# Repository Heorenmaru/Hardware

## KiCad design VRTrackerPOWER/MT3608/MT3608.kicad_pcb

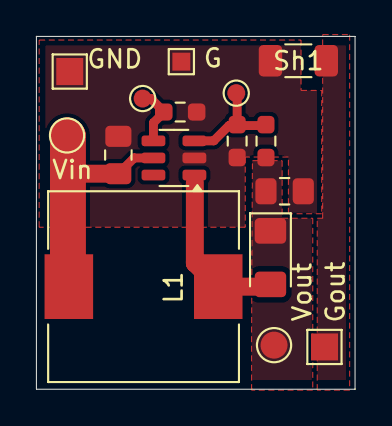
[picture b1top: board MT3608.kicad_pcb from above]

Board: 2 copper layers, 17.7 x 19.6 mm, 16 parts (0 on the bottom side), 7 nets.

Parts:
C2, C3: C; C_0805_2012Metric_Pad1.18x1.45mm_HandSolder
D2: D; D_1206_3216Metric_Pad1.42x1.75mm_HandSolder
E1: EN; TestPoint_Pad_D1.0mm
FB1: FB; TestPoint_Pad_D1.0mm
G: G; TestPoint_Pad_1.0x1.0mm
GND: GND; TestPoint_Pad_1.5x1.5mm
Gout: TestPoint_Pad_1.5x1.5mm
L1: L; L_10.4x10.4_H4.8
R2, R3, R4: R; R_0603_1608Metric_Pad0.98x0.95mm_HandSolder
Sh1: R; R_1206_3216Metric_Pad1.30x1.75mm_HandSolder
U1: MT3608; SOT-23-6
Vin: TestPoint_Pad_D1.5mm
Vout: TestPoint_Pad_D1.5mm

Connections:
unnamed: D2.2 (A), L1.2, U1.1 (SW)
unnamed: C3.1, D2.1 (K), R3.1, Vout.1
unnamed: Gout.1, Sh1.2
unnamed: E1.1, R2.1, U1.4 (EN)
unnamed: FB1.1, R3.2, R4.1, U1.3 (FB)
unnamed: C2.2, C3.2, G.1, GND.1, R2.2, R4.2, Sh1.1, U1.2 (GND)
unnamed: C2.1, L1.1, U1.5 (IN), Vin.1

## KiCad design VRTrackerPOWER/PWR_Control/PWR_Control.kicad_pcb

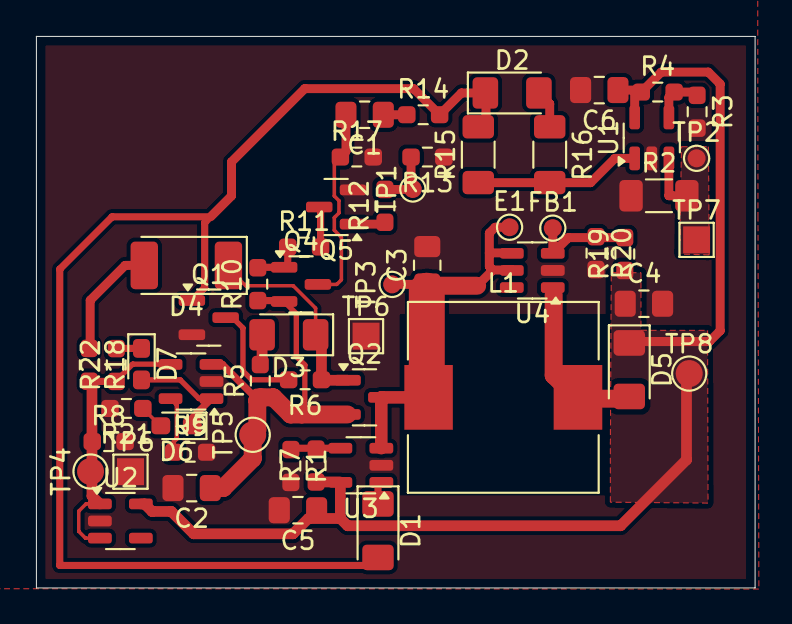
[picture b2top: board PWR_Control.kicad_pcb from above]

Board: 2 copper layers, 39.9 x 30.6 mm, 56 parts (0 on the bottom side), 28 nets.

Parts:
C1, C2, C3, C4, C5, C6: C; C_0805_2012Metric_Pad1.18x1.45mm_HandSolder
D1, D2, D3, D5: D; D_1206_3216Metric_Pad1.42x1.75mm_HandSolder
D4: D; D_2010_5025Metric_Pad1.52x2.65mm_HandSolder
D6, D7: LED; LED_0603_1608Metric_Pad1.05x0.95mm_HandSolder
E1: EN; TestPoint_Pad_D1.0mm
FB1: FB; TestPoint_Pad_D1.0mm
L1: L; L_10.4x10.4_H4.8
Q1, Q5: AO3400A; SOT-23
Q2, Q4: AO3401A; SOT-23
R1, R3, R4, R5, R6, R7, R8, R9, R10, R11, R12, R13, R14, R17, R18, R19, R20, R21, R22: R; R_0603_1608Metric_Pad0.98x0.95mm_HandSolder
R2: 0R5; R_1206_3216Metric_Pad1.30x1.75mm_HandSolder
R15, R16: R; R_1206_3216Metric_Pad1.30x1.75mm_HandSolder
TP1: CONTROL; TestPoint_Pad_D1.0mm
TP2: CUR; TestPoint_Pad_D1.0mm
TP3: PWR; TestPoint_Pad_D1.0mm
TP4: USB; TestPoint_Pad_D1.5mm
TP5: VBAT; TestPoint_Pad_D1.5mm
TP6, TP6#2: GNDi; TestPoint_Pad_1.5x1.5mm
TP7: GNDo; TestPoint_Pad_1.5x1.5mm
TP8: 5V_DC; TestPoint_Pad_D1.5mm
U1, U3: MCP6001-OT; SOT-23-5
U2: MAX40200AUK; SOT-23-5
U4: MT3608; SOT-23-6
U5: MCP73831-2-OT; SOT-23-5

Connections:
+3V6: C3.1, E1.1, L1.1, Q2.3 (D), TP3.1, U3.3 (+), U4.4 (EN), U4.5 (IN)
+3VB: C2.1, Q2.2 (S), Q4.2 (S), R5.1, R10.1, TP5.1, U5.3 (V_{BAT})
+5V: R8.1, R18.2, R22.1, TP4.1, U2.1 (VDD), U2.3 (EN), U5.4 (V_{DD})
+5VD: C4.1, C5.1, C6.1, D5.1 (K), R4.1, R7.1, R19.1, TP8.1, U1.5 (V+), U2.5 (OUT), U3.5 (V+)
GND: C2.2, C3.2, C4.2, C5.2, C6.2, Q1.2 (S), Q5.2 (S), R1.2, R2.1, R3.2, R8.2, R9.2, R13.1, R17.2, R20.2, R21.2, TP6.1, TP6#2.1, U1.2 (V-), U2.2 (GND), U3.2 (V-), U4.2 (GND), U5.2 (V_{SS})
GNDo: R2.2, TP2.1, TP7.1, U1.3 (+)
unnamed: C1.1, R14.1
unnamed: D1.2 (A), D2.1 (K), Q1.1 (G), R14.2, R15.2
unnamed: D1.1 (K), U3.1
unnamed: D2.2 (A), R16.1
unnamed: D3.2 (A), R5.2
unnamed: D3.1 (K), D4.1 (K), Q2.1 (G), R6.1
unnamed: D4.2 (A), R18.1
unnamed: D5.2 (A), L1.2, U4.1 (SW)
unnamed: D6.2 (A), R21.1
unnamed: D6.1 (K), D7.2 (A), U5.1 (STAT)
unnamed: D7.1 (K), R22.2
unnamed: Q1.3 (D), R6.2
unnamed: C1.2, Q4.3 (D), R17.1
unnamed: Q4.1 (G), R10.2, R11.1
unnamed: Q5.3 (D), R11.2
unnamed: Q5.1 (G), R12.1
unnamed: R12.2, R13.2, TP1.1
unnamed: R15.1, R16.2, U1.1
unnamed: R3.1, R4.2, U1.4 (-)
unnamed: R1.1, R7.2, U3.4 (-)
unnamed: FB1.1, R19.2, R20.1, U4.3 (FB)
unnamed: R9.1, U5.5 (PROG)

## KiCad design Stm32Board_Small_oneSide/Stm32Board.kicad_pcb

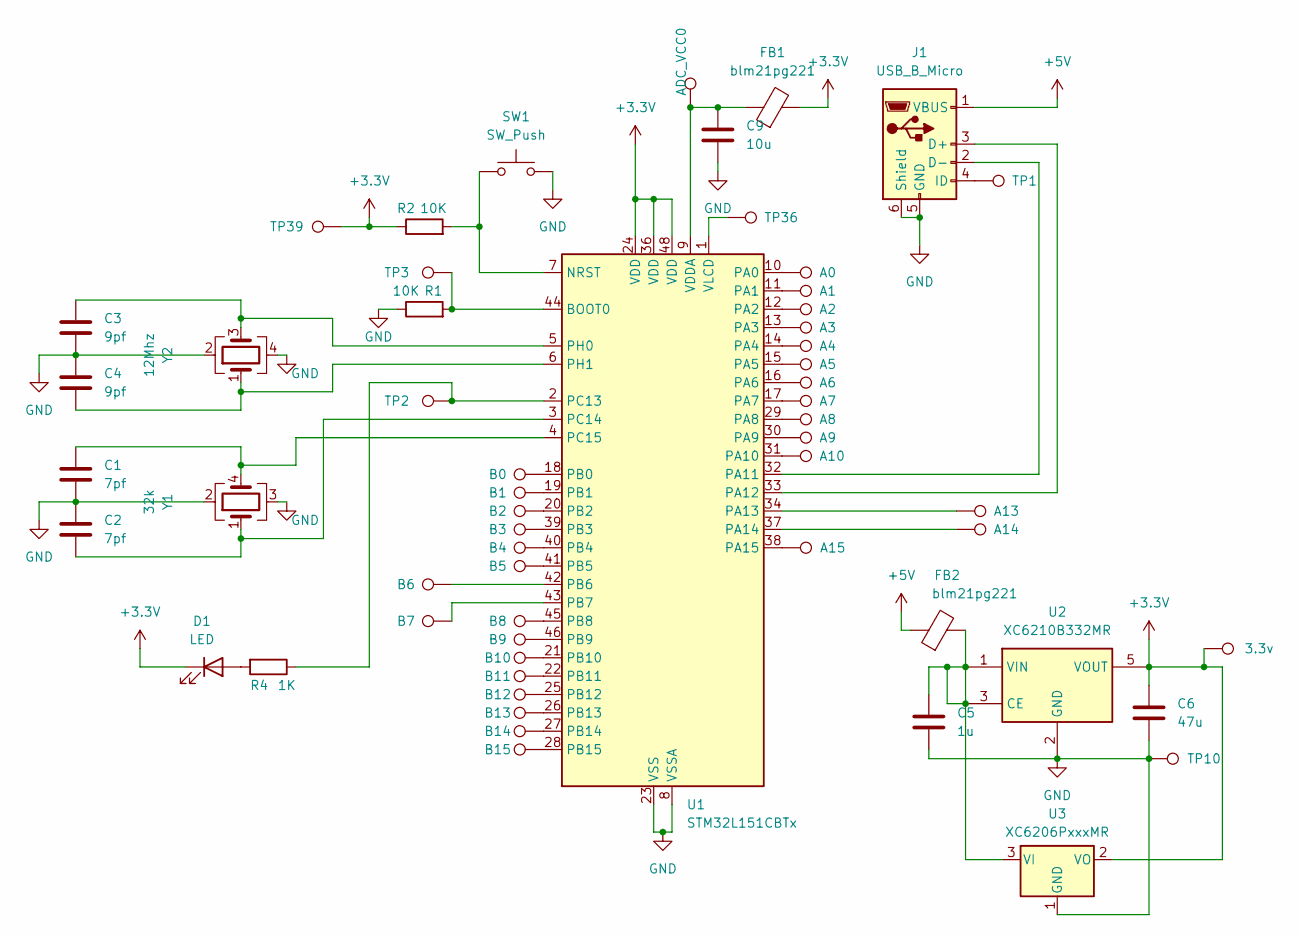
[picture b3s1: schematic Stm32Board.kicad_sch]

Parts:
A0: A0; TestPoint_Pad_D1.0mm
A1: A1; TestPoint_Pad_D1.0mm
A2: A2; TestPoint_Pad_D1.0mm
A3: A3; TestPoint_Pad_D1.0mm
A4: A4; TestPoint_Pad_D1.0mm
A5: A5; TestPoint_Pad_D1.0mm
A6: A6; TestPoint_Pad_D1.0mm
A7: A7; TestPoint_Pad_D1.0mm
A8: A8; TestPoint_Pad_D1.0mm
A9: A9; TestPoint_Pad_D1.0mm
A10: A10; TestPoint_Pad_D1.0mm
A13: SWIO; TestPoint_Pad_D1.0mm
A14: SWCK; TestPoint_Pad_D1.0mm
A15: A15; TestPoint_Pad_D1.0mm
ADC_VCC0: 3.3v; TestPoint_Pad_D1.0mm
B0: B0; TestPoint_Pad_D1.0mm
B1: B1; TestPoint_Pad_D1.0mm
B2: B2; TestPoint_Pad_D1.0mm
B3: B3; TestPoint_Pad_D1.0mm
B4: B4; TestPoint_Pad_D1.0mm
B5: B5; TestPoint_Pad_D1.0mm
B6: B6; TestPoint_Pad_D1.0mm
B7: B7; TestPoint_Pad_D1.0mm
B8: B8; TestPoint_Pad_D1.0mm
B9: B9; TestPoint_Pad_D1.0mm
B10: B10; TestPoint_Pad_D1.0mm
B11: B11; TestPoint_Pad_D1.0mm
B12: B12; TestPoint_Pad_D1.0mm
B13: B13; TestPoint_Pad_D1.0mm
B14: B14; TestPoint_Pad_D1.0mm
B15: B15; TestPoint_Pad_D1.0mm
C1, C2: 7pf; C_0603_1608Metric_Pad1.08x0.95mm_HandSolder
C3, C4: 9pf; C_0603_1608Metric_Pad1.08x0.95mm_HandSolder
C5: 1u; C_0603_1608Metric_Pad1.08x0.95mm_HandSolder
C6: 47u; C_0603_1608Metric_Pad1.08x0.95mm_HandSolder
C9: 10u; C_0603_1608Metric_Pad1.08x0.95mm_HandSolder
D1: LED; LED_0603_1608Metric_Pad1.05x0.95mm_HandSolder
FB1, FB2: blm21pg221; R_0805_2012Metric_Pad1.20x1.40mm_HandSolder
J1: USB_B_Micro; USB_Micro-B_Molex_47346-0001
R1, R2: 10K; R_0603_1608Metric_Pad0.98x0.95mm_HandSolder
R4: 1K; R_0603_1608Metric_Pad0.98x0.95mm_HandSolder
SW1: SW_Push; SW_SPST_B3U-1000P
TP1: USB_ID; TestPoint_Pad_D1.0mm
TP2: C13; TestPoint_Pad_D1.0mm
TP3, TP39: BT0; TestPoint_Pad_D1.0mm
TP9, TP10: 3.3v; TestPoint_Pad_D1.0mm
TP36: VLCD; TestPoint_Pad_D1.0mm
U1: STM32L151CBTx; LQFP-48_7x7mm_P0.5mm
U2: XC6210B332MR; SOT-23-5
U3: XC6206PxxxMR; SOT-23-3
Y1: 32k; Crystal_SMD_SeikoEpson_MC146-4Pin_6.7x1.5mm_HandSoldering
Y2: 12Mhz; Crystal_SMD_3225-4Pin_3.2x2.5mm

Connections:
+3.3V: C6.1, D1.1 (K), FB1.2, R2.1, TP9.1, TP39.1, U1.24 (VDD), U1.36 (VDD), U1.48 (VDD), U2.5 (VOUT), U3.2 (VO); also elsewhere on the board
+5V: FB2.1, J1.1 (VBUS)
GND: C1.2, C2.1, C3.2, C4.1, C5.2, C6.2, C9.2, J1.5 (GND), J1.6 (Shield), R1.1, SW1.2, TP10.1, U1.8 (VSSA), U1.23 (VSS), U1.35 (VSS), U1.47 (VSS), U2.2 (GND), U3.1 (GND), Y1.2, Y1.3, Y2.2, Y2.4
unnamed: D1.2 (A), R4.2
unnamed: J1.3 (D+), U1.33 (PA12)
unnamed: J1.2 (D-), U1.32 (PA11)
unnamed: J1.4 (ID), TP1.1
unnamed: R1.2, TP3.1, U1.44 (BOOT0)
unnamed: R2.2, SW1.1, U1.7 (NRST)
unnamed: A0.1, U1.10 (PA0)
unnamed: A1.1, U1.11 (PA1)
unnamed: A2.1, U1.12 (PA2)
unnamed: A3.1, U1.13 (PA3)
unnamed: A4.1, U1.14 (PA4)
unnamed: A5.1, U1.15 (PA5)
unnamed: A6.1, U1.16 (PA6)
unnamed: A7.1, U1.17 (PA7)
unnamed: A8.1, U1.29 (PA8)
unnamed: A9.1, U1.30 (PA9)
unnamed: A10.1, U1.31 (PA10)
unnamed: A13.1, U1.34 (PA13)
unnamed: A14.1, U1.37 (PA14)
unnamed: A15.1, U1.38 (PA15)
unnamed: B0.1, U1.18 (PB0)
unnamed: B1.1, U1.19 (PB1)
unnamed: B2.1, U1.20 (PB2)
unnamed: B3.1, U1.39 (PB3)
unnamed: B4.1, U1.40 (PB4)
unnamed: B5.1, U1.41 (PB5)
unnamed: B6.1, U1.42 (PB6)
unnamed: B7.1, U1.43 (PB7)
unnamed: B8.1, U1.45 (PB8)
unnamed: B9.1, U1.46 (PB9)
unnamed: B10.1, U1.21 (PB10)
unnamed: B11.1, U1.22 (PB11)
unnamed: B12.1, U1.25 (PB12)
unnamed: B13.1, U1.26 (PB13)
unnamed: B14.1, U1.27 (PB14)
unnamed: B15.1, U1.28 (PB15)
unnamed: R4.1, TP2.1, U1.2 (PC13)
unnamed: C2.2, U1.3 (PC14), Y1.1
unnamed: C1.1, U1.4 (PC15), Y1.4
unnamed: C3.1, U1.5 (PH0), Y2.3
unnamed: C4.2, U1.6 (PH1), Y2.1
unnamed: ADC_VCC0.1, C9.1, FB1.1, U1.9 (VDDA)
unnamed: TP36.1, U1.1 (VLCD)
unnamed: C5.1, FB2.2, U2.1 (VIN), U2.3 (CE), U3.3 (VI)

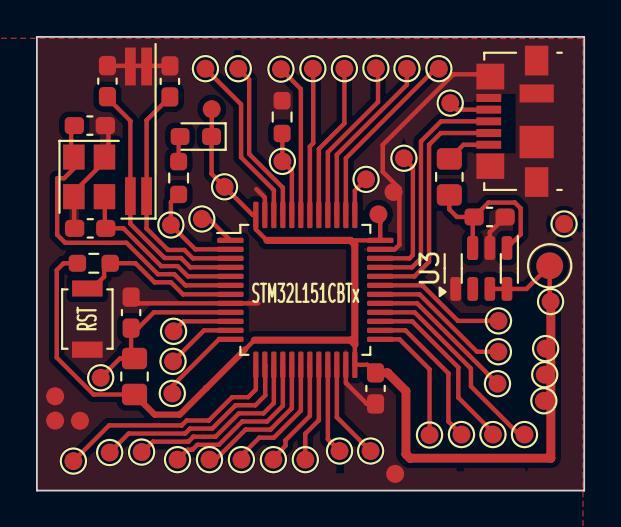
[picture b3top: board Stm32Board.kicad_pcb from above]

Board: 2 copper layers, 30.4 x 25.2 mm, 62 parts (0 on the bottom side), 47 nets.

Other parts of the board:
3.3v CPU: 3.3v; TestPoint_Pad_D2.0mm
TP9#2, TP9#3, TP9#4: 3.3v; TestPoint_Pad_D1.0mm

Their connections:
+3.3V: 3.3v CPU.1, TP9#2.1; also elsewhere on the board

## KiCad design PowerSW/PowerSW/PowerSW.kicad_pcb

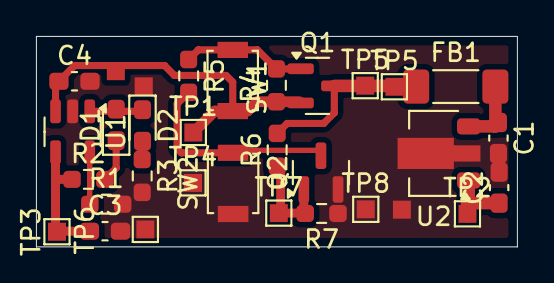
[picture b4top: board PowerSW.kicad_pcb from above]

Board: 2 copper layers, 26.7 x 11.7 mm, 29 parts (0 on the bottom side), 13 nets.

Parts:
C1, C3, C4: 1u; C_0603_1608Metric_Pad1.08x0.95mm_HandSolder
C2: 47u; C_0603_1608Metric_Pad1.08x0.95mm_HandSolder
D1, D2: LED; LED_0603_1608Metric_Pad1.05x0.95mm_HandSolder
FB1: blm21pg221; L_1806_4516Metric_Pad1.45x1.90mm_HandSolder
Q1: AO3401A; SOT-23
Q2: AO3400A; SOT-23
R1: R; R_0603_1608Metric_Pad0.98x0.95mm_HandSolder
R2, R3, R5: 10k; R_0603_1608Metric_Pad0.98x0.95mm_HandSolder
R4, R7: 100k; R_0603_1608Metric_Pad0.98x0.95mm_HandSolder
R6: 1k; R_0603_1608Metric_Pad0.98x0.95mm_HandSolder
SW1, SW2: SW_Push; SW_SPST_B3U-1000P
TP1: PWR; TestPoint_Pad_1.0x1.0mm
TP2: 3v3; TestPoint_Pad_1.0x1.0mm
TP3: CHR; TestPoint_Pad_1.0x1.0mm
TP4, TP6, TP8: GND; TestPoint_Pad_1.0x1.0mm
TP5, TP5#2: OUT; TestPoint_Pad_1.0x1.0mm
TP7: EN; TestPoint_Pad_1.0x1.0mm
U1: MCP73831-2-OT; SOT-23-5
U2: L78L33_SOT89; SOT-89-3

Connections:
+3.3V: C2.1, TP2.1, U2.1 (OUT)
+5V: C3.1, R2.1, TP3.1, U1.4 (V_{DD})
GND: C1.2, C2.2, C3.2, C4.2, Q2.2 (S), R1.2, R3.2, R7.1, SW2.1, TP4.1, TP6.1, TP8.1, U1.2 (V_{SS}), U2.2 (GND)
unnamed: D1.2 (A), D2.1 (K), U1.1 (STAT)
unnamed: D1.1 (K), R2.2
unnamed: D2.2 (A), R3.1
unnamed: Q1.1 (G), R4.2, R5.1, SW1.1
unnamed: C4.1, Q1.2 (S), R4.1, SW1.2, TP1.1, U1.3 (V_{BAT})
unnamed: Q2.3 (D), R5.2, SW2.2
unnamed: Q2.1 (G), R6.1, R7.2, TP7.1
unnamed: R1.1, U1.5 (PROG)
unnamed: C1.1, FB1.2, U2.3 (IN)
VCC: FB1.1, Q1.3 (D), R6.2, TP5#2.1

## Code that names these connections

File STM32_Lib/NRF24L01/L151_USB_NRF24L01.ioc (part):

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Mcu.Name=STM32L151C(6-8-B)Tx
Mcu.Package=LQFP48
Mcu.UserName=STM32L151CBTx
PA11.Mode=Device
PA11.Signal=USB_DM
PA12.Mode=Device
PA12.Signal=USB_DP
PA13.Mode=Serial_Wire
PA13.Signal=SYS_JTMS-SWDIO
PA14.Mode=Serial_Wire
PA14.Signal=SYS_JTCK-SWCLK
PA15.GPIOParameters=GPIO_Speed,GPIO_Label
PA15.GPIO_Label=LED4
PA15.GPIO_Speed=GPIO_SPEED_FREQ_VERY_HIGH
PA15.Signal=GPIO_Output
PA5.Mode=Full_Duplex_Master
PA5.Signal=SPI1_SCK
PA6.Mode=Full_Duplex_Master
PA6.Signal=SPI1_MISO
PA7.Mode=Full_Duplex_Master
PA7.Signal=SPI1_MOSI
PA8.GPIOParameters=GPIO_Label
PA8.GPIO_Label=LED04
PA8.Signal=GPIO_Output
PB10.GPIOParameters=GPIO_Label,GPIO_Speed,PinState
PB10.GPIO_Label=NRF_CS
PB10.GPIO_Speed=GPIO_SPEED_FREQ_VERY_HIGH
PB10.PinState=GPIO_PIN_SET
PB10.Signal=GPIO_Output
PB11.GPIOParameters=GPIO_Label,GPIO_Speed
PB11.GPIO_Label=NRF_CE
PB11.GPIO_Speed=GPIO_SPEED_FREQ_VERY_HIGH
PB11.Signal=GPIO_Output
PB12.GPIOParameters=GPIO_Label
PB12.GPIO_Label=NRF_IRQ
PB12.Signal=GPIO_Input
PB13.GPIOParameters=GPIO_Label
PB13.GPIO_Label=LED01
PB13.Signal=GPIO_Output
PB14.GPIOParameters=GPIO_Label
PB14.GPIO_Label=LED02
PB14.Signal=GPIO_Output
PB15.GPIOParameters=GPIO_Label
PB15.GPIO_Label=LED03
PB15.Signal=GPIO_Output
PB3.GPIOParameters=GPIO_Speed,GPIO_Label
PB3.GPIO_Label=LED3
PB3.GPIO_Speed=GPIO_SPEED_FREQ_VERY_HIGH
PB3.Signal=GPIO_Output
PB4.GPIOParameters=GPIO_Speed,GPIO_Label
PB4.GPIO_Label=LED2
PB4.GPIO_Speed=GPIO_SPEED_FREQ_VERY_HIGH
PB4.Signal=GPIO_Output
PB5.GPIOParameters=GPIO_Speed,PinState,GPIO_Label
PB5.GPIO_Label=LED1
PB5.GPIO_Speed=GPIO_SPEED_FREQ_VERY_HIGH
PB5.PinState=GPIO_PIN_SET
PB5.Signal=GPIO_Output
PB6.GPIOParameters=GPIO_Speed,GPIO_Label
PB6.GPIO_Label=LEDB
PB6.GPIO_Speed=GPIO_SPEED_FREQ_VERY_HIGH
PB6.Signal=GPIO_Output
PB7.GPIOParameters=GPIO_Speed,GPIO_Label
PB7.GPIO_Label=LEDR
PB7.GPIO_Speed=GPIO_SPEED_FREQ_VERY_HIGH
PB7.Signal=GPIO_Output
PC13-WKUP2.GPIOParameters=GPIO_Speed,GPIO_Label
PC13-WKUP2.GPIO_Label=LEDG
PC13-WKUP2.GPIO_Speed=GPIO_SPEED_FREQ_VERY_HIGH
PC13-WKUP2.Signal=GPIO_Output
RCC.HSE_VALUE=12000000
RCC.SYSCLKFreq_VALUE=32000000
RCC.SYSCLKSource=RCC_SYSCLKSOURCE_PLLCLK
board=custom

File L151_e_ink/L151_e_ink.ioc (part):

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Mcu.Name=STM32L151C(6-8-B)Tx
Mcu.Package=LQFP48
Mcu.UserName=STM32L151CBTx
PA11.Mode=Device
PA11.Signal=USB_DM
PA12.Mode=Device
PA12.Signal=USB_DP
PA13.Mode=Serial_Wire
PA13.Signal=SYS_JTMS-SWDIO
PA14.Mode=Serial_Wire
PA14.Signal=SYS_JTCK-SWCLK
PA6.GPIOParameters=GPIO_Label
PA6.GPIO_Label=DISP_RES
PA6.Signal=GPIO_Output
PA7.GPIOParameters=GPIO_Label
PA7.GPIO_Label=DISP_DC
PA7.Signal=GPIO_Output
PB0.GPIOParameters=GPIO_Label
PB0.GPIO_Label=DISP_CS
PB0.Signal=GPIO_Output
PB13.Mode=Full_Duplex_Master
PB13.Signal=SPI2_SCK
PB14.Mode=Full_Duplex_Master
PB14.Signal=SPI2_MISO
PB15.Mode=Full_Duplex_Master
PB15.Signal=SPI2_MOSI
PB6.GPIOParameters=GPIO_Label
PB6.GPIO_Label=LEDB
PB6.Signal=GPIO_Output
PB7.GPIOParameters=GPIO_Label
PB7.GPIO_Label=DISP_BUSY
PB7.Signal=GPIO_Input
PB8.Mode=I2C
PB8.Signal=I2C1_SCL
PB9.Mode=I2C
PB9.Signal=I2C1_SDA
PC13-WKUP2.GPIOParameters=GPIO_Speed,GPIO_Label
PC13-WKUP2.GPIO_Label=LED13
PC13-WKUP2.GPIO_Speed=GPIO_SPEED_FREQ_VERY_HIGH
PC13-WKUP2.Signal=GPIO_Output
RCC.HSE_VALUE=12000000
RCC.SYSCLKFreq_VALUE=32000000
RCC.SYSCLKSource=RCC_SYSCLKSOURCE_PLLCLK
board=custom

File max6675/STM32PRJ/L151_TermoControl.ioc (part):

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Mcu.Name=STM32L151C(6-8-B)Tx
Mcu.Package=LQFP48
Mcu.UserName=STM32L151CBTx
PA10.GPIOParameters=GPIO_Speed,GPIO_Label
PA10.GPIO_Label=SCK
PA10.GPIO_Speed=GPIO_SPEED_FREQ_VERY_HIGH
PA10.Signal=GPIO_Output
PA11.Mode=Device
PA11.Signal=USB_DM
PA12.Mode=Device
PA12.Signal=USB_DP
PA13.Mode=Serial_Wire
PA13.Signal=SYS_JTMS-SWDIO
PA14.Mode=Serial_Wire
PA14.Signal=SYS_JTCK-SWCLK
PA8.GPIOParameters=GPIO_Speed,PinState,GPIO_Label
PA8.GPIO_Label=CS
PA8.GPIO_Speed=GPIO_SPEED_FREQ_VERY_HIGH
PA8.PinState=GPIO_PIN_SET
PA8.Signal=GPIO_Output
PA9.GPIOParameters=GPIO_Label
PA9.GPIO_Label=DAT
PA9.Signal=GPIO_Input
PB1.GPIOParameters=GPIO_Speed,GPIO_Label
PB1.GPIO_Label=DCS
PB1.GPIO_Speed=GPIO_SPEED_FREQ_VERY_HIGH
PB1.Signal=GPIO_Output
PB13.Mode=Full_Duplex_Master
PB13.Signal=SPI2_SCK
PB14.Mode=Full_Duplex_Master
PB14.Signal=SPI2_MISO
PB15.Mode=Full_Duplex_Master
PB15.Signal=SPI2_MOSI
PB2.GPIOParameters=GPIO_Speed,GPIO_Label
PB2.GPIO_Label=DDC
PB2.GPIO_Speed=GPIO_SPEED_FREQ_VERY_HIGH
PB2.Signal=GPIO_Output
PC13-WKUP2.GPIOParameters=GPIO_Speed,PinState,GPIO_Label
PC13-WKUP2.GPIO_Label=L13
PC13-WKUP2.GPIO_Speed=GPIO_SPEED_FREQ_VERY_HIGH
PC13-WKUP2.PinState=GPIO_PIN_SET
PC13-WKUP2.Signal=GPIO_Output
RCC.HSE_VALUE=12000000
RCC.SYSCLKFreq_VALUE=32000000
RCC.SYSCLKSource=RCC_SYSCLKSOURCE_PLLCLK
board=custom

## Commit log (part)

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2024-07-28 NewLib and Uplates
    NewLib NRF24L01
    New Version USBSND
2024-08-01 license
2024-08-01 Add STM32 board
2024-08-01 Added GRB
2024-09-12 add CO2Sensor
2024-11-09 ADS1220
    ADS1220
    LCOS
    Geiger
2025-02-02 more
    + added compass
    + added ads1220
2025-02-11 add e-Inc example
2025-02-12 added e-ink datasheet
2025-04-24 added new prj
2025-06-16 new files
